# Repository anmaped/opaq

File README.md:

# IoT aquarium and pond ecosystem for everyone
#### Release 1.0.7

Main screen |  Settings Screen | Wifi Settings | Graph
:-----------:|:----------------:|:------:|:-------:
 |   |   |  

Supported features:
- Browser-based graphical user interface to control light and power devices of aquarium and pond systems
- Customizable programming actions for nodes such as automation of CO2 injection and temperature management
- Node-based architecture (nodes are authentic, secured with SHA256 signatures)
- Energy cost management that instruct you how to avoid wasting energy

Opaq devices available:

Opaq c1 | Opaq n1 | Opaq n2 | Opaq n3
:------:|:---------:|:---------:|:---------:
the main controller device  | the four channel dimmer device capable to connect with any led lamp (several settings available)  | the power outlet controller node for 220v devices up to 1400w  | battery powered wireless sensor node 

Expected features:
- Support for sensor logging (temperature, humidity, light intensity, PH, Nitrates(NO3))
- Management of peristaltic pumps for automatic fertilization regimes for fresh and salt water aquariums
- Dedicated settings for aquarium and pond systems (pond systems can be controlled by Opaq C1 to automatically perform programmable water changes, and feed fishes; pumps are controlled by programmable actions based on the information provided by water level sensor nodes)
- Dedicated non-introsive water management system based on opaq n2 battery powered 'mope' for sumps and Koi ponds
- Embedded UI

Expected Hardware:
- Opaq N3 (the node for probing PH, light intensity and humidity)

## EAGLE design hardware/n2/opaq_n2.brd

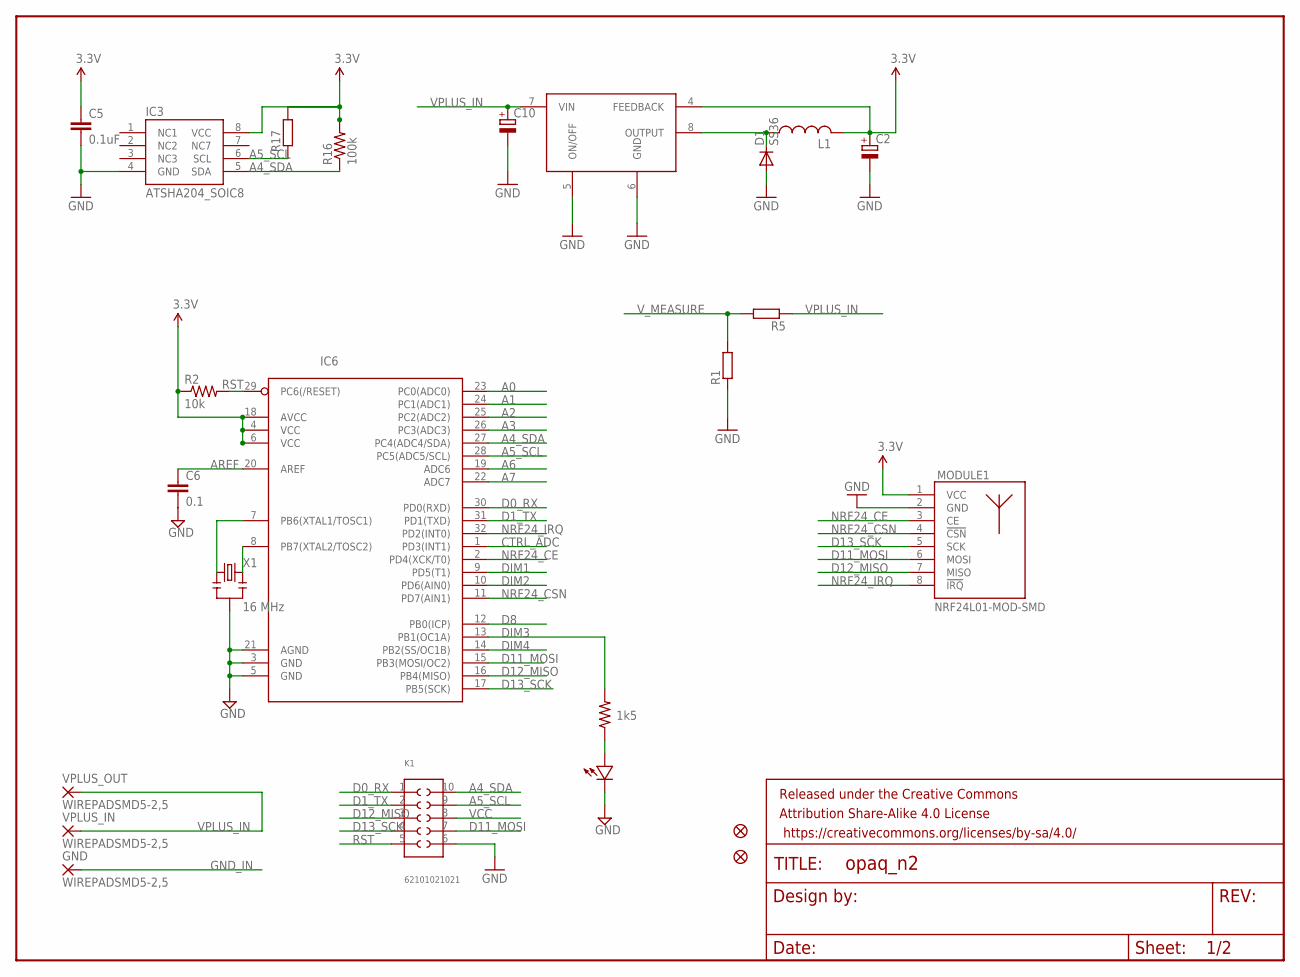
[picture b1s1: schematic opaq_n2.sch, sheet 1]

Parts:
C2: CPOL-EUC/6032-28R; C/6032-28R
C5: 0.1uF; 0805
C6: 0.1; 0603-CAP
C10: CPOL-EUD/7343-31R; D/7343-31R
D1: SS36; SMA-DIODE
DIM: LED0603; 0603-LED
FRAME1: FRAME-LETTER; CREATIVE_COMMONS
GND: WIREPADSMD5-2,5; 5-2,5
IC3: ATSHA204_SOIC8; SOIC8
IC6: ATMega-328; MLF32
IC8: LM2594HV; SO08
JP1, JP2: FIDUCIAL1X2.5; FIDUCIAL-1X2.5
K1: 62101021021
L1: NR6045; 2525
MODULE1: NRF24L01-MOD-SMD; SMD8-MODULE
R1, R5, R17: R-EU_R0805; 0805
R2: 10k; 0603-RES
R3: 1k5; 0603-RES
R16: 100k; 0805
VPLUS_IN: WIREPADSMD5-2,5; 5-2,5
VPLUS_OUT: WIREPADSMD5-2,5; 5-2,5
X1: 16 MHz; RESONATOR-SMD

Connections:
3.3V: C2.+, C5.1, IC3.8 (VCC), IC6.4 (VCC), IC6.6 (VCC), IC6.18 (AVCC), IC8.4 (FEEDBACK), L1.P$1, MODULE1.1 (VCC), R2.1, R16.2, R17.2; also elsewhere on the board
A0: IC6.23 (PC0(ADC0))
A1: IC6.24 (PC1(ADC1))
A2: IC6.25 (PC2(ADC2))
A3: IC6.26 (PC3(ADC3))
A4_SDA: IC3.5 (SDA), IC6.27 (PC4(ADC4/SDA)), K1.10, R16.1; also elsewhere on the board
A5_SCL: IC3.6 (SCL), IC6.28 (PC5(ADC5/SCL)), K1.9, R17.1; also elsewhere on the board
A6: IC6.19 (ADC6)
A7: IC6.22 (ADC7)
AREF: C6.1, IC6.20 (AREF)
CTRL_ADC: IC6.1 (PD3(INT1)); also elsewhere on the board
D0_RX: IC6.30 (PD0(RXD)), K1.1
D1_TX: IC6.31 (PD1(TXD)), K1.2
D8: IC6.12 (PB0(ICP)); also elsewhere on the board
D11_MOSI: IC6.15 (PB3(MOSI/OC2)), K1.7, MODULE1.6 (MOSI); also elsewhere on the board
D12_MISO: IC6.16 (PB4(MISO)), K1.3, MODULE1.7 (MISO); also elsewhere on the board
D13_SCK: IC6.17 (PB5(SCK)), K1.4, MODULE1.5 (SCK); also elsewhere on the board
DIM1: IC6.9 (PD5(T1))
DIM2: IC6.10 (PD6(AIN0))
DIM3: IC6.13 (PB1(OC1A)), R3.2
DIM4: IC6.14 (PB2(SS/OC1B))
GND: C2.-, C5.2, C6.2, C10.-, D1.A, DIM.MINUS, IC3.4 (GND), IC6.3 (GND), IC6.5 (GND), IC6.21 (AGND), IC8.5 (ON/OFF), IC8.6 (GND), K1.6, MODULE1.2 (GND), R1.1, X1.2; also elsewhere on the board
GND_IN: GND.1; also elsewhere on the board
unnamed: IC6.7 (PB6(XTAL1/TOSC1)), X1.1
unnamed: DIM.PLUS, R3.1
unnamed: D1.C, IC8.8 (OUTPUT), L1.P$2
unnamed: IC6.8 (PB7(XTAL2/TOSC2)), X1.3
NRF24_CE: IC6.2 (PD4(XCK/T0)), MODULE1.3 (CE)
NRF24_CSN: IC6.11 (PD7(AIN1)), MODULE1.4 (!CSN)
NRF24_IRQ: IC6.32 (PD2(INT0)), MODULE1.8 (!IRQ)
RST: IC6.29 (PC6(/RESET)), K1.5, R2.2
VCC: K1.8
VPLUS_IN: C10.+, IC8.7 (VIN), R5.1, VPLUS_IN.1, VPLUS_OUT.1
V_MEASURE: R1.2, R5.2; also elsewhere on the board

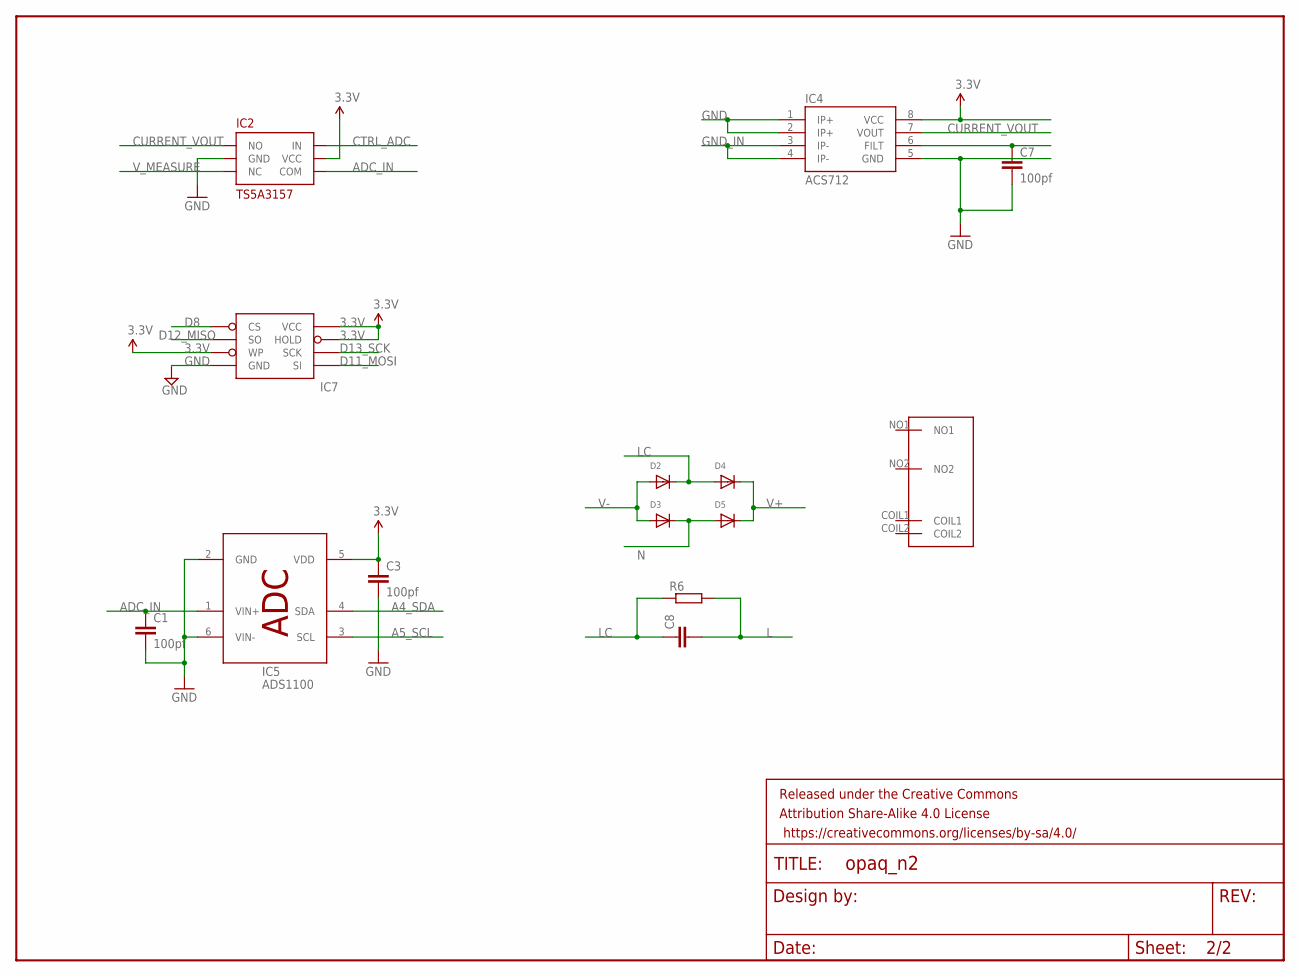
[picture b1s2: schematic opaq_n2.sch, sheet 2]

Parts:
C1, C3, C7: 100pf; 0402-CAP
C8: C-EU225-062X268; C225-062X268
D2, D3, D4, D5: DIODESMA; SMADIODE
FRAME2: FRAME-LETTERNO_PACKAGE; DUMMY
IC2: TS5A3157; SOT23-6
IC4: ACS712; SO08
IC5: ADS1100; SOT23-6
IC7: AT25F512BWIDE_5.3MM; SO08WIDE
R6: R-EU_R2512W; R2512W
U$1: OMRON_G6M-1A

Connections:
3.3V: C3.1, IC2.5 (VCC), IC4.8 (VCC), IC5.5 (VDD), IC7.3 (WP), IC7.7 (HOLD), IC7.8 (VCC); also elsewhere on the board
A4_SDA: IC5.4 (SDA); also elsewhere on the board
A5_SCL: IC5.3 (SCL); also elsewhere on the board
ADC_IN: C1.1, IC2.4 (COM), IC5.1 (VIN+)
CTRL_ADC: IC2.6 (IN); also elsewhere on the board
CURRENT_VOUT: IC2.1 (NO), IC4.7 (VOUT)
D8: IC7.1 (CS); also elsewhere on the board
D11_MOSI: IC7.5 (SI); also elsewhere on the board
D12_MISO: IC7.2 (SO); also elsewhere on the board
D13_SCK: IC7.6 (SCK); also elsewhere on the board
FILT: C7.1, IC4.6 (FILT)
GND: C1.2, C3.2, C7.2, IC2.2 (GND), IC4.1 (IP+), IC4.2 (IP+), IC4.5 (GND), IC5.2 (GND), IC5.6 (VIN-), IC7.4 (GND); also elsewhere on the board
GND_IN: IC4.3 (IP-), IC4.4 (IP-); also elsewhere on the board
L: C8.2, R6.2
LC: C8.1, D2.C, D4.A, R6.1
N: D3.C, D5.A
V+: D4.C, D5.C
V-: D2.A, D3.A
V_MEASURE: IC2.3 (NC); also elsewhere on the board

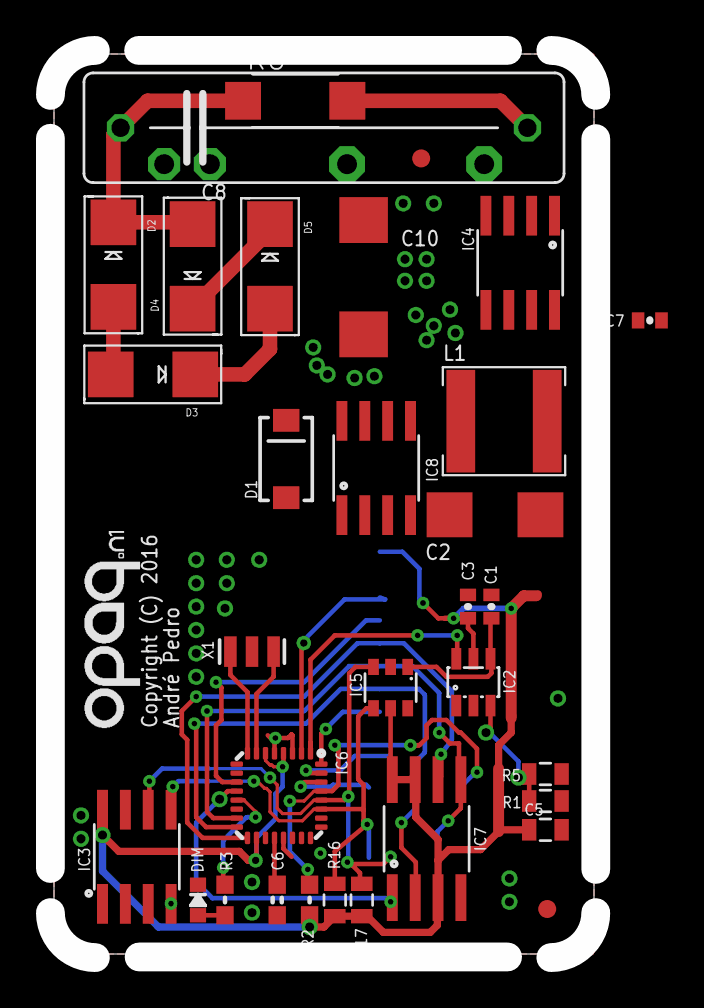
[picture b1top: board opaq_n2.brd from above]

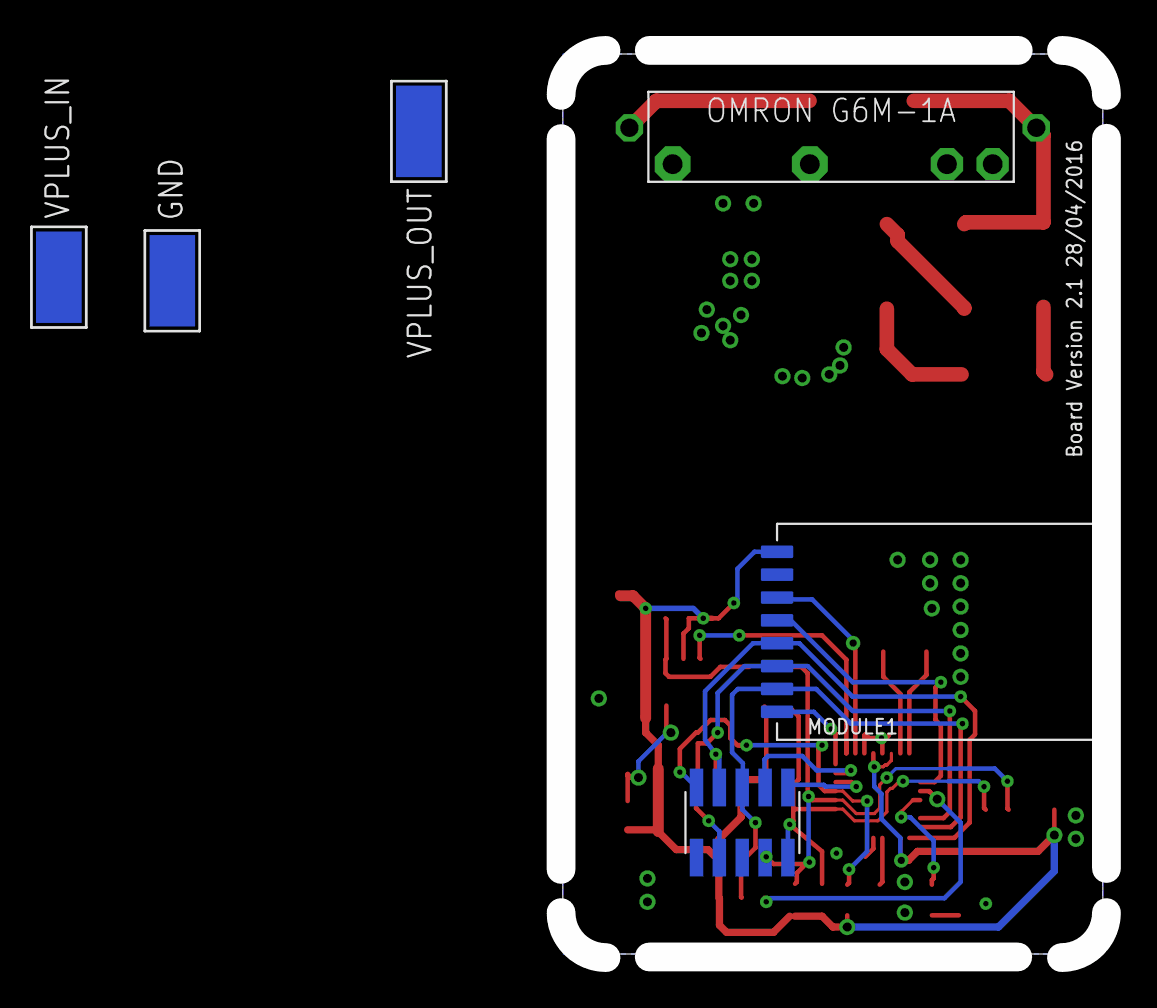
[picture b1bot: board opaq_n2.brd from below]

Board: 2 copper layers, 30.0 x 50.0 mm, 40 parts (6 on the bottom side), 32 nets.

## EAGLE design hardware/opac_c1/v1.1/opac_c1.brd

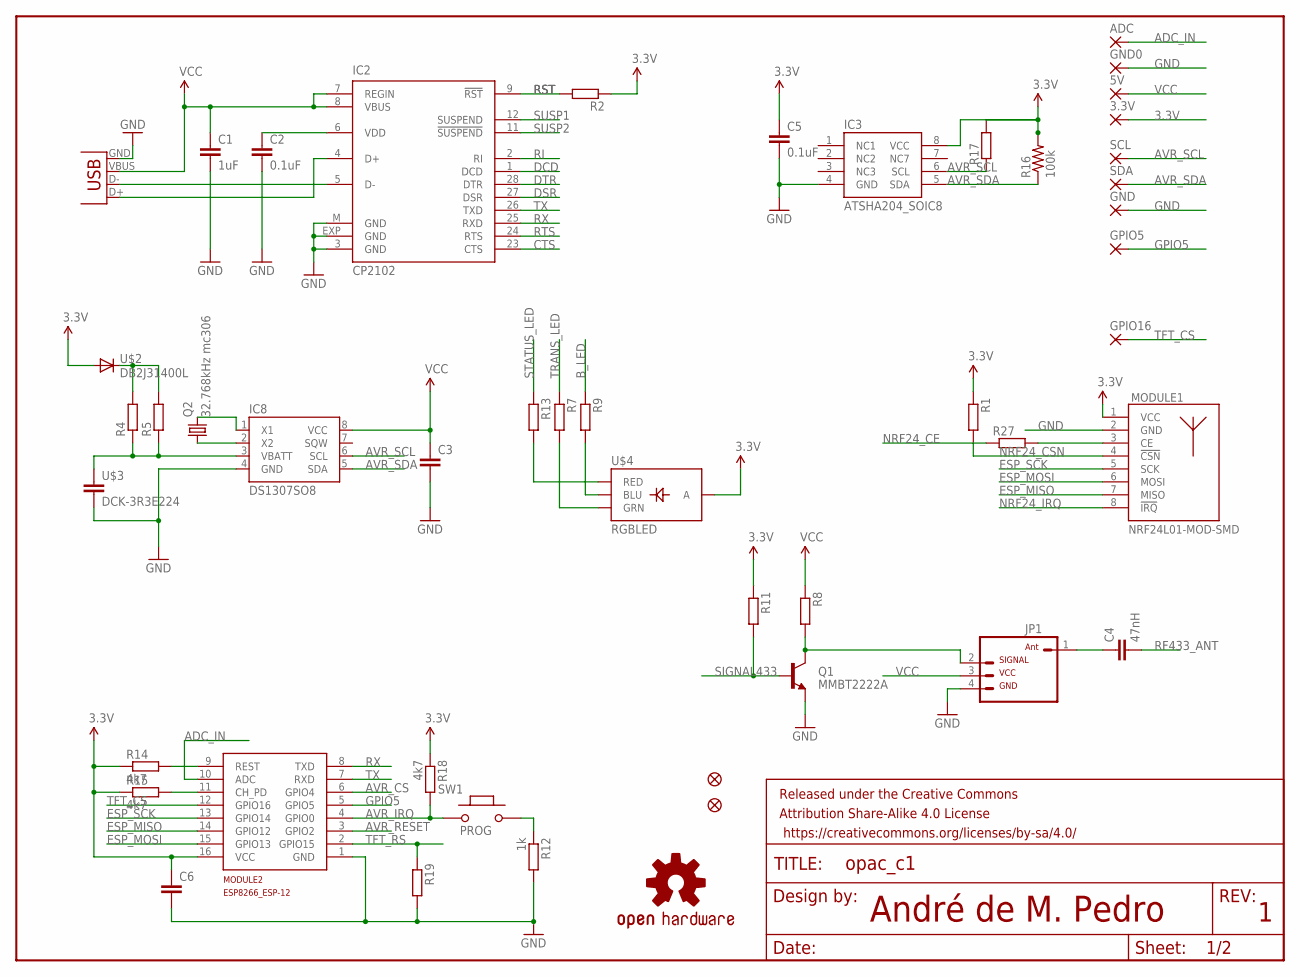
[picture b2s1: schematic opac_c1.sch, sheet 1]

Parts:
3.3V, 5V: SMD2; SMD1,27-2,54
ADC: SMD2; SMD1,27-2,54
C1: 1uF; 0603
C2: 0.1uF; 0603
C3, C6: C-EUC0805K; C0805K
C4: 47nH; C0603K
C5: 0.1uF; 0805
FRAME1: FRAME-LETTER; CREATIVE_COMMONS
GND, GND0: SMD2; SMD1,27-2,54
GPIO5, GPIO16: SMD2; SMD1,27-2,54
IC2: CP2102; MLP28
IC3: ATSHA204_SOIC8; SOIC8
IC8: DS1307SO8; SO08
JP1: RF433SMD; 1X04-SMD
JP2, JP3: FIDUCIAL1X2.5; FIDUCIAL-1X2.5
LOGO1: OSHW-LOGOL; OSHW-LOGO-L
MODULE1: NRF24L01-MOD-SMD; SMD8-MODULE
MODULE2: ESP8266_ESP-12; ESP8266-ESP12
Q1: MMBT2222A; SOT23-3
Q2: 32.768kHz mc306; MC-306
R1, R4, R5, R8, R11, R17, R19, R27: R-EU_R0805; 0805
R2, R7, R9, R13: R-EU_R0603; R0603
R12: 1k; 0805
R14, R15, R18: 4k7; 0805
R16: 100k; 0805
SCL: SMD2; SMD1,27-2,54
SDA: SMD2; SMD1,27-2,54
SW1: PROG; 157SW; PARTNO RS 682-1421
U$2: DB2J31400L; SMINI2-F5-B
U$3: DCK-3R3E224
U$4: RGBLED; RGBLED0603
USB1: USB-MICROB

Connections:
3.3V: 3.3V.1, C5.1, C6.1, IC3.8 (VCC), MODULE1.1 (VCC), MODULE2.16 (VCC), R1.1, R2.1, R11.1, R14.1, R15.1, R16.2, R17.2, R18.1, U$2.P$2 (A), U$4.P$3 (A); also elsewhere on the board
ADC_IN: ADC.1, MODULE2.10 (ADC)
AVR_CS: MODULE2.6 (GPIO4); also elsewhere on the board
AVR_IRQ: MODULE2.4 (GPIO0), R18.2, SW1.1; also elsewhere on the board
AVR_RESET: MODULE2.3 (GPIO2); also elsewhere on the board
AVR_SCL: IC3.6 (SCL), IC8.6 (SCL), R17.1, SCL.1; also elsewhere on the board
AVR_SDA: IC3.5 (SDA), IC8.5 (SDA), R16.1, SDA.1; also elsewhere on the board
B_LED: R9.1; also elsewhere on the board
CTS: IC2.23 (CTS)
DCD: IC2.1 (DCD)
DSR: IC2.27 (DSR)
DTR: IC2.28 (DTR)
ESP_MISO: MODULE1.7 (MISO), MODULE2.14 (GPIO12); also elsewhere on the board
ESP_MOSI: MODULE1.6 (MOSI), MODULE2.15 (GPIO13); also elsewhere on the board
ESP_SCK: MODULE1.5 (SCK), MODULE2.13 (GPIO14); also elsewhere on the board
GND: C1.2, C2.2, C3.2, C5.2, C6.2, GND.1, GND0.1, IC2.3 (GND), IC2.EXP (GND), IC2.M (GND), IC3.4 (GND), IC8.4 (GND), JP1.4 (2), MODULE1.2 (GND), MODULE2.1 (GND), Q1.2 (E), R12.2, R19.2, U$3.P$1 (2), USB1.GND; also elsewhere on the board
GPIO5: GPIO5.1, MODULE2.5 (GPIO5)
unnamed: IC8.3 (VBATT), R4.1, R5.1, U$3.P$2 (1)
unnamed: IC8.2 (X2), Q2.1
unnamed: R4.2, R5.2, U$2.P$1 (C)
unnamed: C2.1, IC2.6 (VDD)
unnamed: IC8.1 (X1), Q2.4 (2)
unnamed: R13.2, U$4.P$1 (RED)
unnamed: R12.1, SW1.2
unnamed: IC2.5 (D-), USB1.D-
unnamed: R7.2, U$4.P$2 (GRN)
unnamed: IC2.4 (D+), USB1.D+
unnamed: JP1.2 (3), Q1.3 (C), R8.2
unnamed: R9.2, U$4.P$4 (BLU)
unnamed: MODULE1.3 (CE), R27.2
unnamed: C4.1, JP1.1 (4)
unnamed: MODULE2.9 (REST), R14.2
unnamed: MODULE2.11 (CH_PD), R15.2
NRF24_CE: R27.1; also elsewhere on the board
NRF24_CSN: MODULE1.4 (!CSN), R1.2; also elsewhere on the board
NRF24_IRQ: MODULE1.8 (!IRQ); also elsewhere on the board
RF433_ANT: C4.2
RI: IC2.2 (RI)
RST: IC2.9 (!RST), R2.2
RTS: IC2.24 (RTS)
RX: IC2.25 (RXD), MODULE2.8 (TXD)
SIGNAL433: Q1.1 (B), R11.2; also elsewhere on the board
STATUS_LED: R13.1; also elsewhere on the board
SUSP1: IC2.12 (SUSPEND)
SUSP2: IC2.11 (!SUSPEND)
TFT_CS: GPIO16.1, MODULE2.12 (GPIO16); also elsewhere on the board
TFT_RS: MODULE2.2 (GPIO15), R19.1; also elsewhere on the board
TRANS_LED: R7.1; also elsewhere on the board
TX: IC2.26 (TXD), MODULE2.7 (RXD)
VCC: 5V.1, C1.1, C3.1, IC2.7 (REGIN), IC2.8 (VBUS), IC8.8 (VCC), JP1.3 (1), R8.1, USB1.VBUS; also elsewhere on the board

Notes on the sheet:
André de M. Pedro

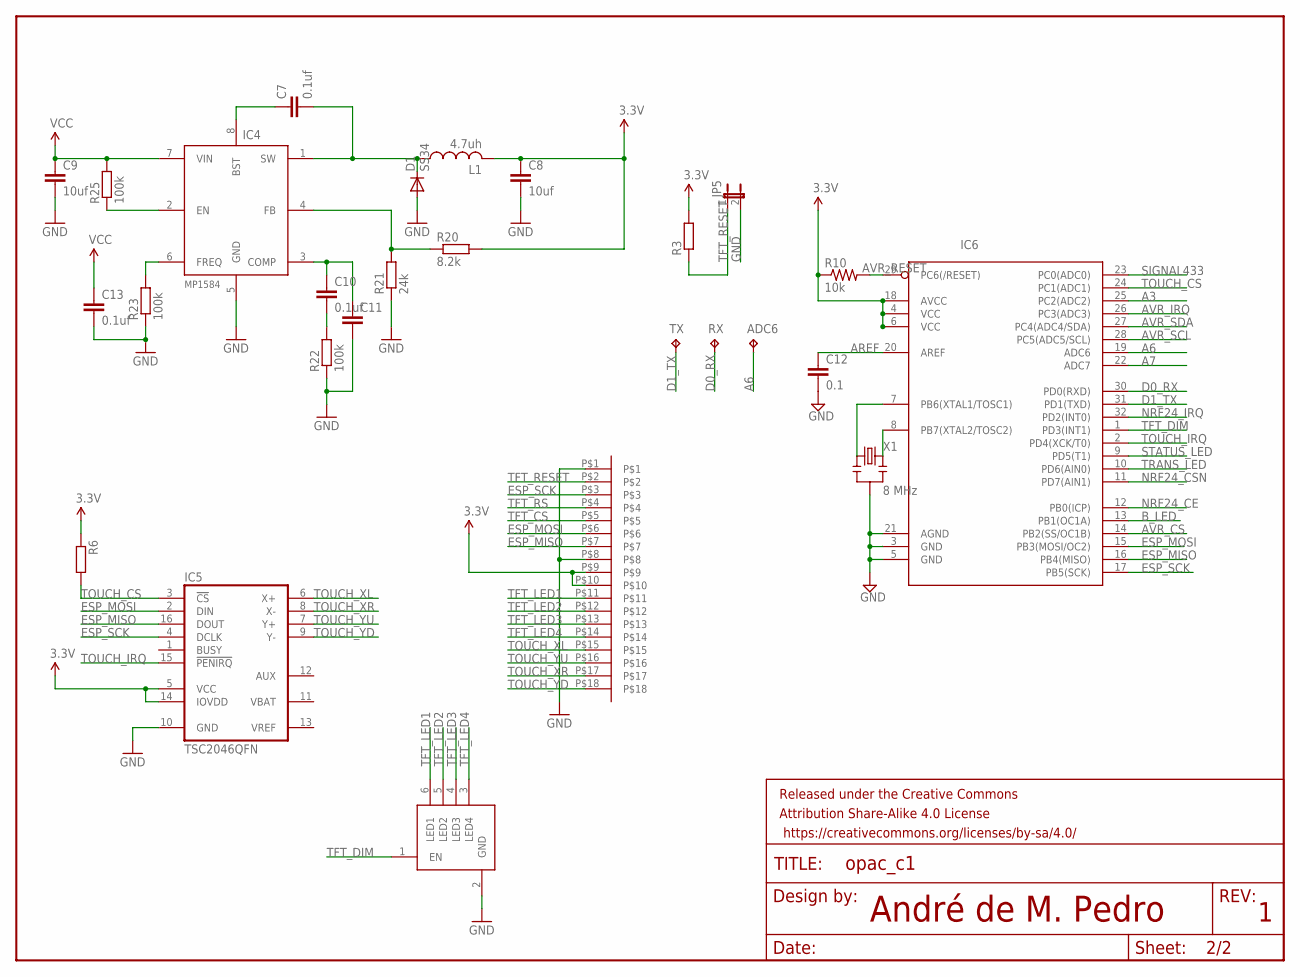
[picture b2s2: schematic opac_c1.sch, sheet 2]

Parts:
ADC6: TPTP09R; TP09R
C7, C10, C13: 0.1uf; C0603
C8, C9: 10uf; C3216
C11: C-EUC0603; C0603
C12: 0.1; 0805
D1: SS34; SMA-DIODE
FRAME2: FRAME-LETTER; CREATIVE_COMMONS
IC4: MP1584; SO08-EPAD
IC5: TSC2046QFN; QFN16-4X4
IC6: ATMega-328; MLF32
IC7: RT9300; SOT23-6
JP5: JUMPER-2SMD-NO; SJ_2S-NO
L1: 4.7uh; 2525
R3: R-EU_R0402; R0402
R6: R-EU_R0805; 0805
R10: 10k; 0603-RES
R20: 8.2k; R0603
R21: 24k; R0603
R22, R23, R25: 100k; R0603
RX: TPTP10SQ; TP10SQ
TX: TPTP10SQ; TP10SQ
U$1: CONNECTOR8P0.8; CONNECTOR18P0.8
X1: 8 MHz; RESONATOR-SMD

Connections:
3.3V: C8.1, IC5.5 (VCC), IC5.14 (IOVDD), IC6.4 (VCC), IC6.6 (VCC), IC6.18 (AVCC), L1.P$1, R3.2, R6.1, R10.1, R20.2, U$1.P$9, U$1.P$10; also elsewhere on the board
A3: IC6.25 (PC2(ADC2))
A6: ADC6.TP, IC6.19 (ADC6)
A7: IC6.22 (ADC7)
AREF: C12.1, IC6.20 (AREF)
AVR_CS: IC6.14 (PB2(SS/OC1B)); also elsewhere on the board
AVR_IRQ: IC6.26 (PC3(ADC3)); also elsewhere on the board
AVR_RESET: IC6.29 (PC6(/RESET)), R10.2; also elsewhere on the board
AVR_SCL: IC6.28 (PC5(ADC5/SCL)); also elsewhere on the board
AVR_SDA: IC6.27 (PC4(ADC4/SDA)); also elsewhere on the board
B_LED: IC6.13 (PB1(OC1A)); also elsewhere on the board
D0_RX: IC6.30 (PD0(RXD)), RX.TP
D1_TX: IC6.31 (PD1(TXD)), TX.TP
ESP_MISO: IC5.16 (DOUT), IC6.16 (PB4(MISO)), U$1.P$7; also elsewhere on the board
ESP_MOSI: IC5.2 (DIN), IC6.15 (PB3(MOSI/OC2)), U$1.P$6; also elsewhere on the board
ESP_SCK: IC5.4 (DCLK), IC6.17 (PB5(SCK)), U$1.P$3; also elsewhere on the board
GND: C8.2, C9.2, C11.2, C12.2, C13.2, D1.A, IC4.5 (GND), IC5.10 (GND), IC6.3 (GND), IC6.5 (GND), IC6.21 (AGND), IC7.2 (GND), JP5.2, R21.1, R22.1, R23.1, U$1.P$1, U$1.P$8, X1.2; also elsewhere on the board
unnamed: IC6.7 (PB6(XTAL1/TOSC1)), X1.1
unnamed: IC6.8 (PB7(XTAL2/TOSC2)), X1.3
unnamed: C7.2, D1.C, IC4.1 (SW), L1.P$2
unnamed: C7.1, IC4.8 (BST)
unnamed: IC4.4 (FB), R20.1, R21.2
unnamed: IC4.2 (EN), R25.1
unnamed: IC4.6 (FREQ), R23.2
unnamed: C10.1, C11.1, IC4.3 (COMP)
unnamed: C10.2, R22.2
NRF24_CE: IC6.12 (PB0(ICP)); also elsewhere on the board
NRF24_CSN: IC6.11 (PD7(AIN1)); also elsewhere on the board
NRF24_IRQ: IC6.32 (PD2(INT0)); also elsewhere on the board
SIGNAL433: IC6.23 (PC0(ADC0)); also elsewhere on the board
STATUS_LED: IC6.9 (PD5(T1)); also elsewhere on the board
TFT_CS: U$1.P$5; also elsewhere on the board
TFT_DIM: IC6.1 (PD3(INT1)), IC7.1 (EN)
TFT_LED1: IC7.6 (LED1), U$1.P$11
TFT_LED2: IC7.5 (LED2), U$1.P$12
TFT_LED3: IC7.4 (LED3), U$1.P$13
TFT_LED4: IC7.3 (LED4), U$1.P$14
TFT_RESET: JP5.1, R3.1, U$1.P$2
TFT_RS: U$1.P$4; also elsewhere on the board
TOUCH_CS: IC5.3 (!CS), IC6.24 (PC1(ADC1)), R6.2
TOUCH_IRQ: IC5.15 (!PENIRQ), IC6.2 (PD4(XCK/T0))
TOUCH_XL: IC5.6 (X+), U$1.P$15
TOUCH_XR: IC5.8 (X-), U$1.P$17
TOUCH_YD: IC5.9 (Y-), U$1.P$18
TOUCH_YU: IC5.7 (Y+), U$1.P$16
TRANS_LED: IC6.10 (PD6(AIN0)); also elsewhere on the board
VCC: C9.1, C13.1, IC4.7 (VIN), R25.2; also elsewhere on the board

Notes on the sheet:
André de M. Pedro

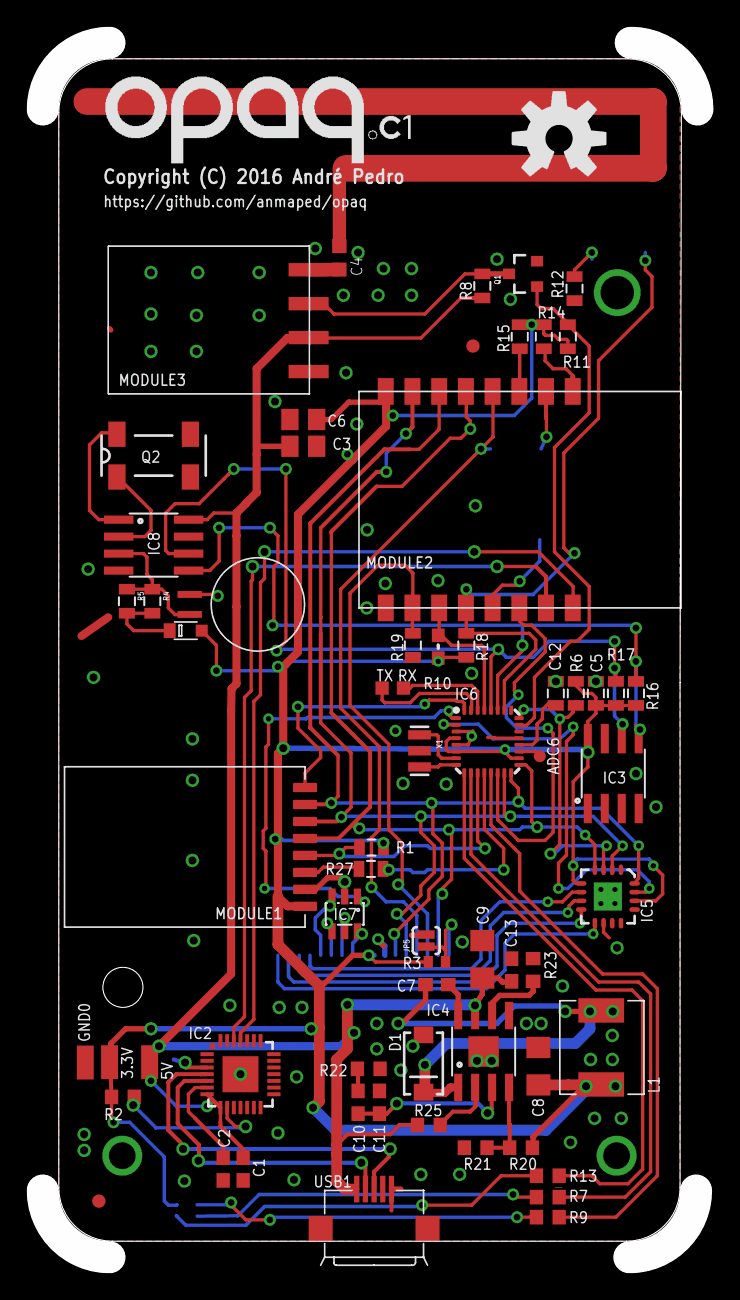
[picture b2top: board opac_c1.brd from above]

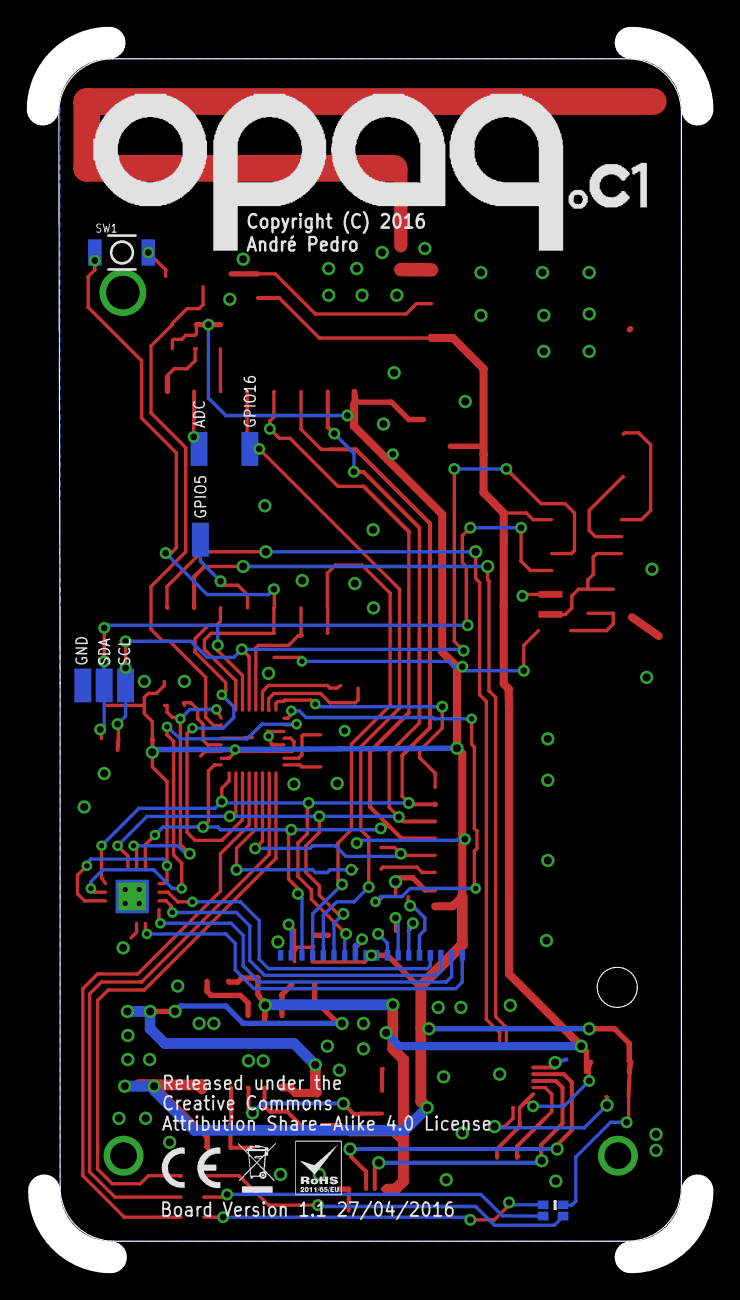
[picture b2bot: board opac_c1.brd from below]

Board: 2 copper layers, 49.0 x 90.9 mm, 77 parts (9 on the bottom side), 66 nets.

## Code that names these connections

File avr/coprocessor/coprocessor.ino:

#include "atsha204.h"
#include "ds1307.h"
#include "protocol.h"
#include "rf433.h"
#include "version.h"

#include <RtcDS1307.h>
#include <SPI.h>
#include <Scheduler.h>
#include <Wire.h>

#include <SHA204.h>
#include <SHA204Definitions.h>
#include <SHA204I2C.h>

// pinout
#define PIN_NRF24_CSN 7
#define PIN_NRF24_CE 8
#define PIN_TOUCH_CS A1

#define RED_LED 5
#define GREEN_LED 6
#define BLUE_LED 9

volatile byte command = 0;
volatile bool comunicating = 0;
volatile byte count = 0;


// the setup function runs once when you press reset or power the board
void setup() {

  delay(100);

  Serial.begin(9600);

  pinMode(11, INPUT);
  pinMode(12, OUTPUT);
  pinMode(13, INPUT);
  pinMode(10, INPUT);

  // turn on SPI in slave mode
  SPCR |= _BV(SPE);

  // turn on interrupts
  SPCR |= _BV(SPIE);

  /**
   * Pin Change Interrupt enable on PCINT0 (PB0)
   */
  PCICR |= _BV(PCIE0);
  PCMSK0 = 0;
  PCMSK0 |= _BV(PCINT2);

  // Turn interrupts on.
  sei();

  // initialize digital pin 13 as an output.
  pinMode(5, OUTPUT); // green
  pinMode(6, OUTPUT); // red
  pinMode(9, OUTPUT); // blue

  pinMode(PIN_NRF24_CSN, OUTPUT); // pin NRF24_CSN
  pinMode(PIN_NRF24_CE, OUTPUT);  // pin NRF24_CE
  pinMode(PIN_TOUCH_CS, OUTPUT);  // pin TOUCH_CS
  digitalWrite(PIN_NRF24_CSN, HIGH);
  digitalWrite(PIN_NRF24_CE, HIGH);
  digitalWrite(PIN_TOUCH_CS, HIGH);

  pinMode(3, OUTPUT);
  analogWrite(3, 255);

  // real-time clock
  rtc.Begin();
  // rtc.SetDateTime(RtcDateTime(2016,5,25,5,34,0));
  rtc.SetIsRunning(true);

  sha204dev.init();
  wakeupExample();       // dummy
  serialNumberExample(); // dummy

  // RF433 setup
  Rf433_transmitter.set_pin(A0);
  Rf433_transmitter.set_encoding(Rf433_transmitter.CHANON_DIO_DEVICE);

  Scheduler.start(setup_status, loop_status);
  Scheduler.start(setup_com, loop_com);
  Scheduler.start(setup_warning, loop_warning);
}

void setup_status() { pinMode(GREEN_LED, OUTPUT); }

void loop_status() {
  if (!comunicating) {
    blink(GREEN_LED, 500);
  } else {
    digitalWrite(GREEN_LED, LOW);
    delay(1000);
  }
}

void setup_com() { pinMode(BLUE_LED, OUTPUT); }

void loop_com() {
  digitalWrite(BLUE_LED, LOW);
  delay(100);
  digitalWrite(BLUE_LED, HIGH);
  delay(500);
  digitalWrite(BLUE_LED, LOW);
  delay(100);
  digitalWrite(BLUE_LED, HIGH);
  delay(2000);
}

void setup_warning() { pinMode(RED_LED, OUTPUT); }

void loop_warning() {
  if (true) {
    digitalWrite(RED_LED, HIGH);
    delay(1000);
  } else {
    blink(RED_LED, 500);
  }
}

void blink(int pin, unsigned int ms) {
  digitalWrite(pin, HIGH);
  delay(ms);
  digitalWrite(pin, LOW);
  delay(ms);
}

ISR(PCINT0_vect) {
  if (!(PINB & B00000100)) {
    PORTD |= B10000000;
    PORTC |= B00000010;
  } else {
    command = 0;
  }
}

// SPI interrupt routine
ISR(SPI_STC_vect) {
  byte data = SPDR;

  switch (command) {
  // no command? then this is the command
  case 0:
    SPDR = 1;
    command = data;
    count = 0;
    break;

  case ID_DS1307_GETDATA:

    if (count < sizeof(RtcDateTime))
      SPDR = ds1307(count);

    count++;
    comunicating = true;
    break;

  case ID_DS1307_SETDATA:

    if (count < sizeof(RtcDateTime)) {
      setDs1307(data, count);

      if (count == sizeof(RtcDateTime) - 1) {
        // update clock
        setClockActive = true;
      }
    }

    count++;
    break;

  case ID_NRF24_CSN:

    if (count == 0) {
      if (data == 0x01) {
        // digitalWrite(PIN_NRF24_CSN, HIGH);
        PORTD |= B10000000;
      } else {
        // digitalWrite(PIN_NRF24_CSN, LOW);
        PORTD &= B01111111;
      }
    }

    command = 0;
    break;

  case ID_NRF24_CE:

    if (data == HIGH) {
      digitalWrite(PIN_NRF24_CE, HIGH);
    } else {
      digitalWrite(PIN_NRF24_CE, LOW);
    }

    command = 0;
    break;

  case ID_ATSHA402:

    SPDR = serialNumber[count];

    count++;
    break;

  case ID_TSC2046_CSN:

    if (data == HIGH) {
      // digitalWrite(PIN_TOUCH_CS, HIGH);
      PORTC |= B00000010;
    } else {
      // digitalWrite(PIN_TOUCH_CS, LOW);
      PORTC &= B11111101;
    }

    command = 0;
    break;

  case ID_RF433_STREAM:

    // byte data = SPDR;
    // enqueue stream
    enqueue_stream(data, count);
    SPDR = data;

    count++;
    break;

  case ID_DIM_TFT:

    analogWrite(3, data);
    break;

  case ID_STATUS:
    
    byte *statusbitvector = (byte *)&st;
    SPDR = statusbitvector[count];

    count++;
    break;

  } // end of switch

} // end of interrupt service routine (ISR) SPI_STC_vect

void loop() {

  delay(10);

  if (setClockActive) {
    setClockActive = false;
    rtc.SetDateTime(clock);
  } else {
    clock = rtc.GetDateTime();
  }

  rf433();
}

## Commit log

2015-08-28 Initial readme.
2015-08-28 First release of opaq. Release 1.0.
2015-09-09 Web interface for power outlets has been added. Devices are now managed by tasks.
2015-09-09 Script that generates charts of opaq monitor.
2015-09-18 Minor changes. Opensource license policy was included in some source files.
2015-10-07 OPAQ is now under evaluation for the next release v1.0.1 Support for dealing with several power outlets at the same time have been added.
2015-10-08 Readme screenshot added.
2015-10-08 Readme changes for version 1.0.1.
2015-10-08 New readme.
2015-10-08 Power outlets are now visible in the light settings as piecewise functions.
2015-10-12 Tools to update the firmware.
2015-10-13 New working binary version.
2015-10-13 New firmware. Speedup of the webpage loading. Reboot and factory settings buttons have been inserted.
2015-10-14 Client SSID and PWD size have been increased.
2015-10-14 Several features are corrected. They are - Client SSID and PWD size have been increased. - Speedup of the webpage loading. - Reboot and factory settings buttons have been inserted. - Power outlet iss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
2015-10-16 SPIFFS support is added. Issues of power outlet timings are corrected. Labels are assigned to each power socket.
2015-10-16 New release 1.0.2.
    Several issues have been corrected. They are
    - Webpage loading performs fast by calculating the content size before send it.
    - Client SSID and PWD length are increased.
    - Power outlet GUI related issues are solved.
    - Power outlet timings issues are solved.
    New features:
2015-10-19 Minor changes.
2015-10-22 Power outlet issues were solved.
2015-10-23 Issues of webpages were solved.
2015-10-26 Release 1.0.3. This release contains tweaks for timings of the rf switches device driver. Rf switches can now initialize without randomly binding when opaq c1 is running. Several graphical user inter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
2015-10-27 Constraints and delays for NRF24 were added.
2015-11-04 Opaq C1 board v1.0 has released. Source-files are available over the CC-SA license.
2015-11-04 Revision 1 of opac.c1 board.
2015-11-05 Opaq.c1 revision 2.
2015-11-11 Release 1.0.3 rev.1 - Readme has been changed. - Small corrections on UI. - Scripts for graphics have been modified to support mobile devices.
2015-11-11 Readme minor changes.
2015-11-12 Image has been coupled to readme.
2015-11-12 Image has been re-sized.
2015-11-18 Opac n1 hardware released.
2015-11-18 Readme was updated.
2015-11-19 Opaq n1 board revision 1.
2015-11-22 Opaq C1 hardware revision 3.
2015-11-24 Opaq n1 hardware revision 2.
2016-04-13 Minor changes. - opaq connection has been improved. - IOT is now working (update through internet is available). - mdns support has been added(default domain 'opaq.local'). - websockets server has be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
2016-05-10 Opaq c1 version 1.1 has been released.
2016-05-10 Opaq n1 version 2.1 has been released.
2016-05-10 Release 1.0.4
2016-07-02 Opaq c1 supports iaqua graphical interface.
    The touch screen and the 320x240 tft is now supported.
    Added features:
    - file storage manager using JSON for opaq settings.
    - touch screen calibration.
    - coprocessor program to interact with real-time clock, cypher chip (SHA204), and expansion of the GPIO.
    - ISP programmer for AVR coprocessor.
2016-07-02 Several issues of the Opaq c1 hardware have been fixed.
2016-07-04 Minor changes. Opaq c1 is now capable to send OOK messages at 433mhz in an efficient way.
2016-07-04 Opaq c1 hardware has been updated.
    - pull-up resistor have been added to RF433 signal.
2016-07-15 Opaq WEB interface has been changed. It now support asynchronous request.
2016-08-04 Opaq c1 Web GUI for light dimmer plug-in has been implemented. Clock for local GUI has been updated as well.
2016-08-13 Added the new fixes for opaq c1 hardware.
2016-08-13 Added support for using hash maps for RF433 power outlets. Minor fixes for web ui, opaq c1 configuration files, and co-processor interface have also been done.
2016-08-13 Added two modules for external libraries.
2016-08-13 Added Arduinojson repository.
2016-08-23 Pre release of the opaq c1 version 1.0.5
    Added features:
    - loading screen for the opaq iaqua
    - power devices plugin
    - light dimmer devices plugin
2016-08-23 Updated version of the opaq c1 hardware.
2016-08-23 Removed unnecessary files.
2016-09-05 Added the hardcoded recovery page for download and upload of the filesystem using tar archives. Firmware update is also allowed. Notes SPIFFS filesystem is using 64-bit filename size.
2016-09-13 Added the feature for inter-process communication based on command triggering. - native atomic C++11 for byte size is now supported.
2016-09-22 Release of version 1.0.6 Several fixes: - Fixed the webpage loading speed and some timeouts. - Added the cli interface with support for file uploading. - Added support for using standard unix command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
2016-09-22 Readme updated with new screenshots.
2016-09-22 Uploaded the binary files for opaq c1.
2016-09-23 Remove unnecessary binary files from source code.
2016-09-25 Programming of co-processor is now built-in. Command line includes the 'update' command to upload the firmware. Support for dimming light of the opaq c1 touch version is also included in the command 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
2016-10-17 Added the structure for the opaq n1 firmware.
2016-10-25 Updated the Opaq n1 firmware to read the external temperature and the input voltage. Added the support for the external flash. Renamed the folder of the Opaq n1 hardware.
2016-10-25 Optimized the memory consumption by removing plain strings from Opaq c1 firmware.
2016-10-25 Added scheduler library for esp8266 multi-tasking. Updated the LinkedList for the local repository.
2016-10-25 Updated the submodules.
2016-10-27 Added atsha204 and DS18B20 compatibility in order to use the same gpio.
2016-10-31 Split hardware files from source code.
2016-11-03 Updated opaq n1 firmware to communicate with a mesh of rf24 nodes. - non-volatile memory tested - atsha204 cypher chip tested - temperature sensor ds18b20 tested - voltage sensor tested RF24 ACK bit 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
2016-11-03 Fixed pinMode for SPI CS pins.
2016-11-15 Added support for connecting opaq c1 to thingspeak and share sensor data from opaq nodes. Several fixes have been done for opaq c1 firmware including stopping the 433mhz transmitter when idle, and op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
2016-11-26 Updated the readme file.
2020-04-05 Fix ESPAsyncTCP version. Add build script.
2020-04-05 Fix submodules.
2020-04-06 Fix zmodem. Update scheduler to master. Update esp8266 core.
2020-04-06 Update README to version 1.0.7.
2020-04-06 Fix small issues. Set version 1.0.7.
2020-04-06 Fix code style standards.
2020-04-08 Fix task layout and multithread lock and unlock.
2020-04-09 Add opaqc1-coproc and opaqn1 build.
2020-04-10 Add coprocessor cli status.
2020-04-10 Add version tag to opaqc1 and coprocessor fw.
2020-04-13 Fix ArduinoJson to version 6. Fix ESPAsyncWebServer to redefinitions of LinkedList using a different namespace.
2020-04-25 Enable ci.
2020-04-25 Fix esp8266 scheduller library.
2020-04-26 Add web query for nrf24 connected devices.
2020-04-27 Add support to create the Web UI archive.
2020-04-27 Add support to build sett and iaqua tar files.
2020-05-03 Add support for esp8266 core 2.7.0.
2020-05-17 Fix STA mode and websocket reconnection. Correct typos in Opaq_recovery.h. Add script to do ota updates.
2020-05-21 Build google-closure-compiler in travis-ci.
2020-05-22 Fix touch calibrate command and websocket.
2020-05-23 Add serial loopback to show console on websockets.
2020-05-24 Prettify .html files. Compress .html files with gzip.
2020-05-29 Add RDP smothing function to compress data collected from sensors.
2020-06-01 Fix recursive Ramer-Douglas-Peucker line simplification.
2020-06-18 Fix esp8266 stack. Fix console command 'stack'.
2020-06-19 Add non-recursive rdp algorithm.

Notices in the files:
hardware/n2/opaq_n2.brd:
Copyright (C) 2016
hardware/opac_c1/v1.1/opac_c1.brd:
Copyright (C) 2016 André Pedro
Released under the
Creative Commons
Attribution Share-Alike 4.0 License
parts and their libraries:
SparkFun-Aesthetics: Licensing: Creative Commons ShareAlike 4.0 International - https://creativecommons.org/licenses/by-sa/4.0
SparkFun-Aesthetics: Released under the Creative Commons Attribution Share-Alike 4.0 License
SparkFun-Aesthetics: https://creativecommons.org/licenses/by-sa/4.0
